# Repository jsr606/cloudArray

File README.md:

# cloud array
github repository for the tech side of the permanent installation "cloud array".

this installation lives permanently at [søndervangskolen](https://soendervangskolen.aarhus.dk/) in viby, århus, denmark. you can see the installation from the inside as well as the outside 24 hours a day, all year.

for more information visit this website www.jacobremin.com/cloudArray

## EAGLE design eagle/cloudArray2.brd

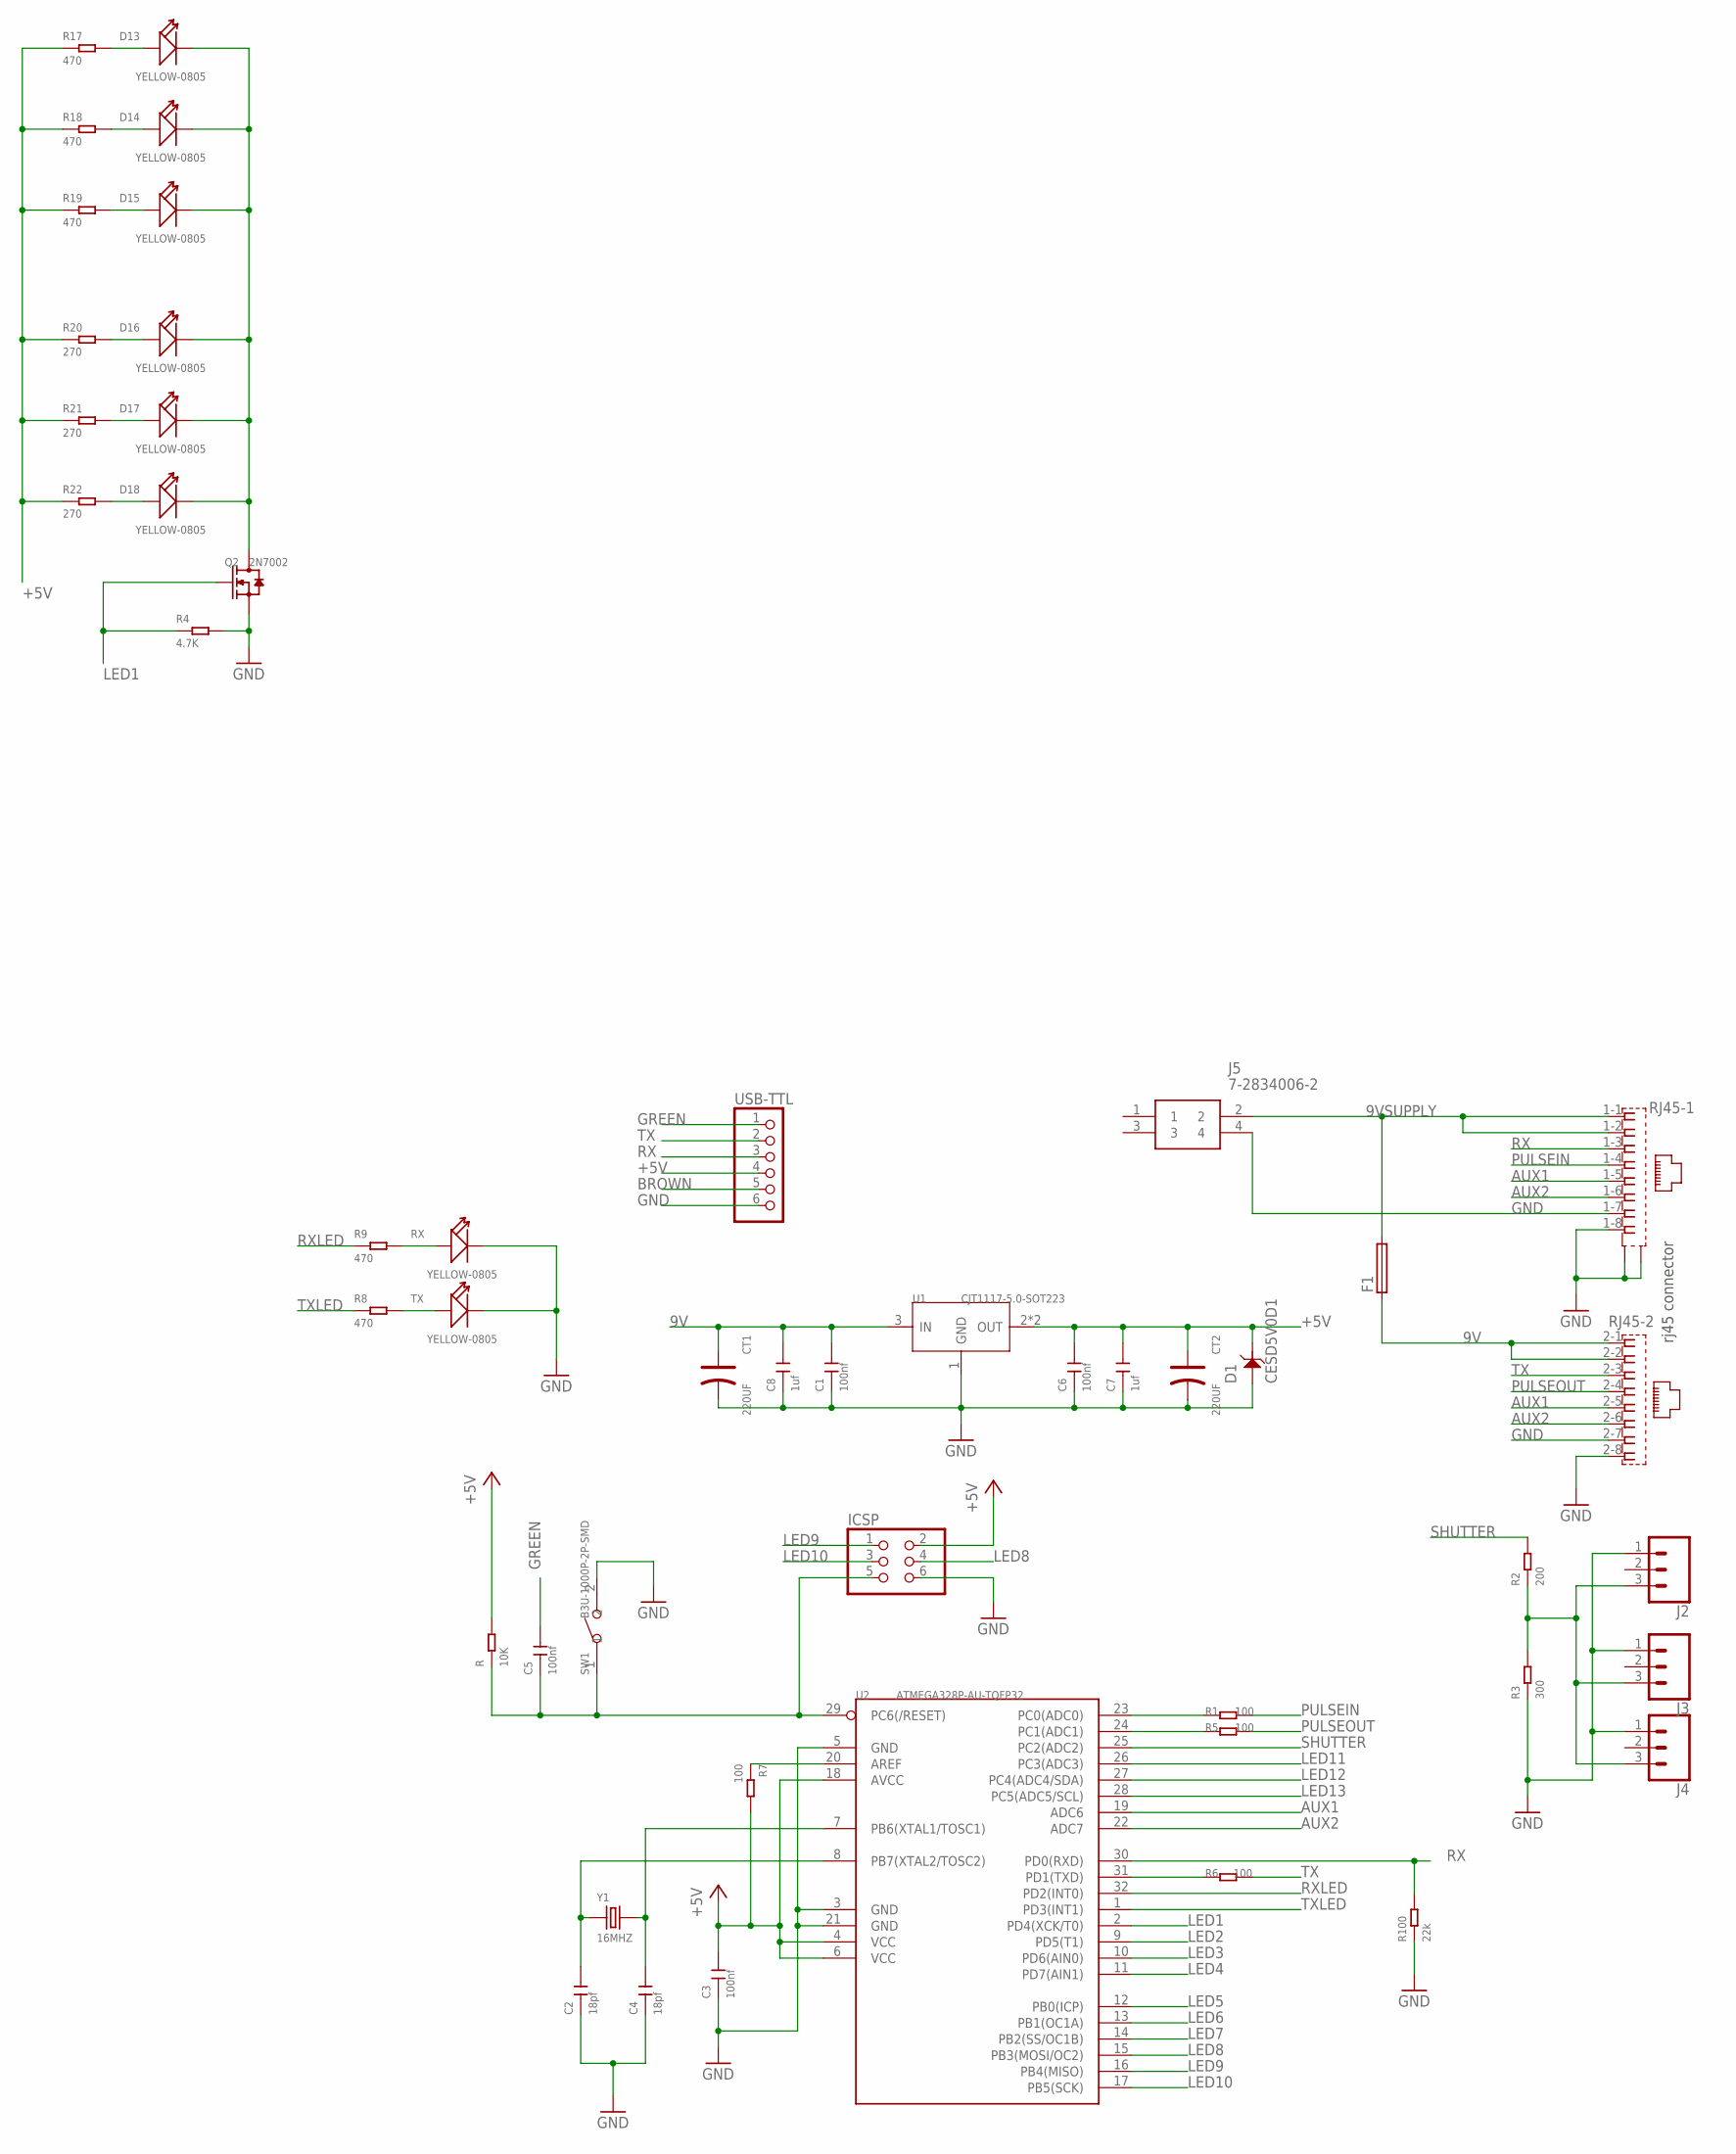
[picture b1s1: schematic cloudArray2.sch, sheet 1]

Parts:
C1, C3, C5, C6: 100nf; C0805
C2, C4: 18pf; C0805
C7, C8: 1uf; C0805
CT1, CT2: 220UF; ELECTRO-SMD-C-6MM
D1: CESD5V0D1; SOD-123
D13, D14, D15, D16, D17, D18: YELLOW-0805; LED-0805
F1: SH22,5A
ICSP: PINHD-2X3; 2X03
J2, J3, J4: 455-1750-1-ND; 1X03
J5: 7-2834006-2; 728340062
Q2: 2N7002; SOT-23
R: 10K; R0805
R1, R5, R6, R7: 100; R0805
R2: 200; R0805
R3: 300; R0805
R4: 4.7K; R0805
R8, R9, R17, R18, R19: 470; R0805
R20, R21, R22: 270; R0805
R100: 22k; R0805
RJ45: 557570-1
RX: YELLOW-0805; LED-0805
SW1: B3U-1000P-2P-SMD; SW2-2.6-3.0X2.5X1.2+0.4MM
TX: YELLOW-0805; LED-0805
U1: CJT1117-5.0-SOT223; SOT-223
U2: ATMEGA328P-AU-TQFP32; TQFP32-0.8-7X7MM
USB-TTL: PINHD-1X6; 1X06
Y1: 16MHZ; X2-SMD-5.0X3.2X1.3MM

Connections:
9V: C1.2, C8.2, CT1.+, F1.1, RJ45.2-1 (1), RJ45.2-2 (2), U1.3 (IN)
9VSUPPLY: F1.2, J5.2, RJ45.1-1 (1), RJ45.1-2 (2)
+5V: C3.2, C6.2, C7.2, CT2.+, D1.- (2), ICSP.2, R.2, R7.2, R17.1, R18.1, R19.1, R20.1, R21.1, R22.1, U1.2 (OUT), U1.TER (OUT), U2.4 (VCC), U2.6 (VCC), U2.18 (AVCC), USB-TTL.4; also elsewhere on the board
A0: R1.2, U2.23 (PC0(ADC0))
A1: R5.2, U2.24 (PC1(ADC1))
AREF: R7.1, U2.20 (AREF)
AUX1: RJ45.1-5 (5), RJ45.2-5 (5), U2.19 (ADC6)
AUX2: RJ45.1-6 (6), RJ45.2-6 (6), U2.22 (ADC7)
BROWN: USB-TTL.5
GND: C1.1, C2.1, C3.1, C4.1, C6.1, C7.1, C8.1, CT1.-, CT2.-, D1.+ (1), ICSP.6, J2.1, J3.1, J4.1, J5.4, Q2.2 (S), R3.1, R4.2, R100.1, RJ45.1-7 (7), RJ45.1-8 (8), RJ45.2-7 (7), RJ45.2-8 (8), RJ45.G1 (S2), RJ45.G3 (S1), RX.-, SW1.2, TX.-, U1.1 (GND), U2.3 (GND), U2.5 (GND), U2.21 (GND), USB-TTL.6; also elsewhere on the board
GREEN: C5.2, USB-TTL.1
LED1: Q2.1 (G), R4.1, U2.2 (PD4(XCK/T0))
LED2: U2.9 (PD5(T1)); also elsewhere on the board
LED3: U2.10 (PD6(AIN0)); also elsewhere on the board
LED4: U2.11 (PD7(AIN1)); also elsewhere on the board
LED5: U2.12 (PB0(ICP)); also elsewhere on the board
LED6: U2.13 (PB1(OC1A)); also elsewhere on the board
LED7: U2.14 (PB2(SS/OC1B)); also elsewhere on the board
LED8: ICSP.4, U2.15 (PB3(MOSI/OC2)); also elsewhere on the board
LED9: ICSP.1, U2.16 (PB4(MISO)); also elsewhere on the board
LED10: ICSP.3, U2.17 (PB5(SCK)); also elsewhere on the board
LED11: U2.26 (PC3(ADC3)); also elsewhere on the board
LED12: U2.27 (PC4(ADC4/SDA)); also elsewhere on the board
LED13: U2.28 (PC5(ADC5/SCL)); also elsewhere on the board
unnamed: D13.-, D14.-, D15.-, D16.-, D17.-, D18.-, Q2.3 (D)
unnamed: C2.2, U2.8 (PB7(XTAL2/TOSC2)), Y1.1
unnamed: C4.2, U2.7 (PB6(XTAL1/TOSC1)), Y1.2
unnamed: R6.2, U2.31 (PD1(TXD))
unnamed: R8.2, TX.+
unnamed: J2.3, J3.3, J4.3, R2.1, R3.2
unnamed: R9.2, RX.+
unnamed: D13.+, R17.2
unnamed: D14.+, R18.2
unnamed: D15.+, R19.2
unnamed: D16.+, R20.2
unnamed: D17.+, R21.2
unnamed: D18.+, R22.2
PULSEIN: R1.1, RJ45.1-4 (4)
PULSEOUT: R5.1, RJ45.2-4 (4)
RESET: C5.1, ICSP.5, R.1, SW1.1, U2.29 (PC6(/RESET))
RX: R100.2, RJ45.1-3 (3), U2.30 (PD0(RXD)), USB-TTL.3
RXLED: R9.1, U2.32 (PD2(INT0))
SHUTTER: R2.2, U2.25 (PC2(ADC2))
TX: R6.1, RJ45.2-3 (3), USB-TTL.2
TXLED: R8.1, U2.1 (PD3(INT1))

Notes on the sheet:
rj45 connector

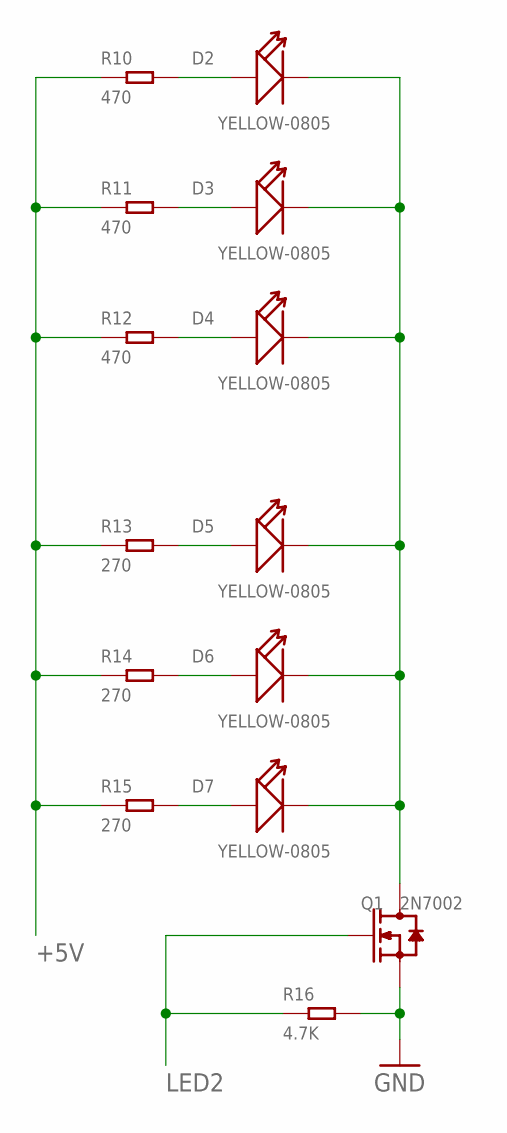
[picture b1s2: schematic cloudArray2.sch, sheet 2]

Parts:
D2, D3, D4, D5, D6, D7: YELLOW-0805; LED-0805
Q1: 2N7002; SOT-23
R10, R11, R12: 470; R0805
R13, R14, R15: 270; R0805
R16: 4.7K; R0805

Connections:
+5V: R10.1, R11.1, R12.1, R13.1, R14.1, R15.1; also elsewhere on the board
GND: Q1.2 (S), R16.2; also elsewhere on the board
LED2: Q1.1 (G), R16.1; also elsewhere on the board
unnamed: D2.+, R10.2
unnamed: D3.+, R11.2
unnamed: D4.+, R12.2
unnamed: D5.+, R13.2
unnamed: D6.+, R14.2
unnamed: D7.+, R15.2
unnamed: D2.-, D3.-, D4.-, D5.-, D6.-, D7.-, Q1.3 (D)

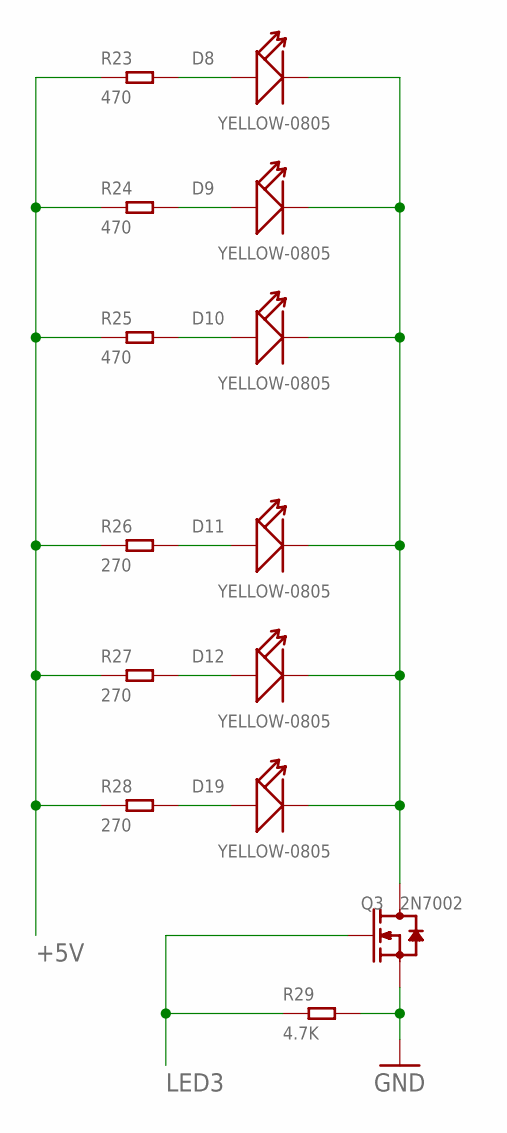
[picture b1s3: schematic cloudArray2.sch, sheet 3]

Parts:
D8, D9, D10, D11, D12, D19: YELLOW-0805; LED-0805
Q3: 2N7002; SOT-23
R23, R24, R25: 470; R0805
R26, R27, R28: 270; R0805
R29: 4.7K; R0805

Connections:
+5V: R23.1, R24.1, R25.1, R26.1, R27.1, R28.1; also elsewhere on the board
GND: Q3.2 (S), R29.2; also elsewhere on the board
LED3: Q3.1 (G), R29.1; also elsewhere on the board
unnamed: D8.+, R23.2
unnamed: D9.+, R24.2
unnamed: D10.+, R25.2
unnamed: D11.+, R26.2
unnamed: D12.+, R27.2
unnamed: D19.+, R28.2
unnamed: D8.-, D9.-, D10.-, D11.-, D12.-, D19.-, Q3.3 (D)

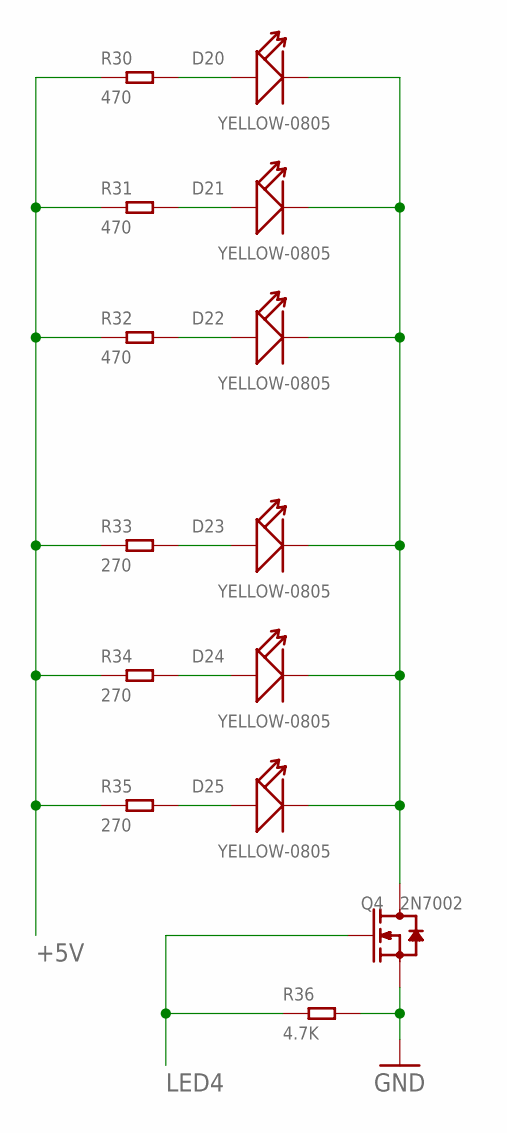
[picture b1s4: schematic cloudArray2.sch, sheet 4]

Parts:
D20, D21, D22, D23, D24, D25: YELLOW-0805; LED-0805
Q4: 2N7002; SOT-23
R30, R31, R32: 470; R0805
R33, R34, R35: 270; R0805
R36: 4.7K; R0805

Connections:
+5V: R30.1, R31.1, R32.1, R33.1, R34.1, R35.1; also elsewhere on the board
GND: Q4.2 (S), R36.2; also elsewhere on the board
LED4: Q4.1 (G), R36.1; also elsewhere on the board
unnamed: D20.+, R30.2
unnamed: D21.+, R31.2
unnamed: D22.+, R32.2
unnamed: D23.+, R33.2
unnamed: D24.+, R34.2
unnamed: D25.+, R35.2
unnamed: D20.-, D21.-, D22.-, D23.-, D24.-, D25.-, Q4.3 (D)

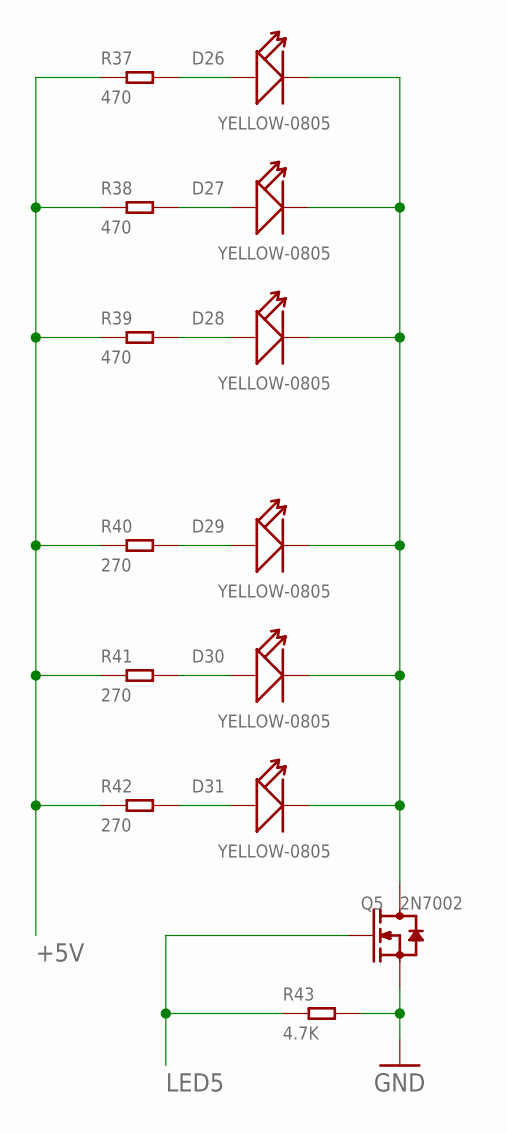
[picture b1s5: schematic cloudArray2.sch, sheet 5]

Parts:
D26, D27, D28, D29, D30, D31: YELLOW-0805; LED-0805
Q5: 2N7002; SOT-23
R37, R38, R39: 470; R0805
R40, R41, R42: 270; R0805
R43: 4.7K; R0805

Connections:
+5V: R37.1, R38.1, R39.1, R40.1, R41.1, R42.1; also elsewhere on the board
GND: Q5.2 (S), R43.2; also elsewhere on the board
LED5: Q5.1 (G), R43.1; also elsewhere on the board
unnamed: D26.+, R37.2
unnamed: D27.+, R38.2
unnamed: D28.+, R39.2
unnamed: D29.+, R40.2
unnamed: D30.+, R41.2
unnamed: D31.+, R42.2
unnamed: D26.-, D27.-, D28.-, D29.-, D30.-, D31.-, Q5.3 (D)

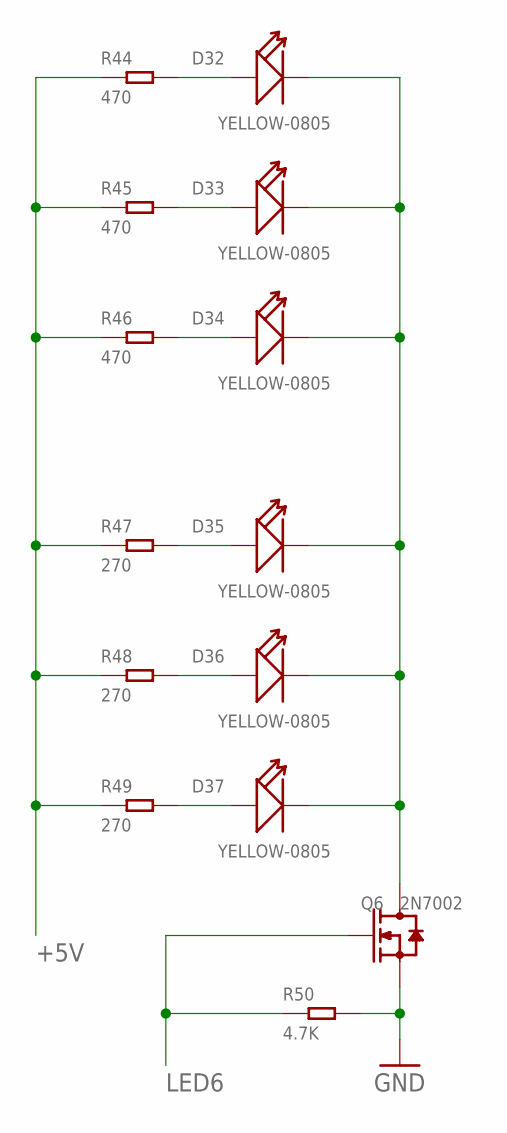
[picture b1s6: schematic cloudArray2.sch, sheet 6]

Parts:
D32, D33, D34, D35, D36, D37: YELLOW-0805; LED-0805
Q6: 2N7002; SOT-23
R44, R45, R46: 470; R0805
R47, R48, R49: 270; R0805
R50: 4.7K; R0805

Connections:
+5V: R44.1, R45.1, R46.1, R47.1, R48.1, R49.1; also elsewhere on the board
GND: Q6.2 (S), R50.2; also elsewhere on the board
LED6: Q6.1 (G), R50.1; also elsewhere on the board
unnamed: D32.+, R44.2
unnamed: D33.+, R45.2
unnamed: D34.+, R46.2
unnamed: D35.+, R47.2
unnamed: D36.+, R48.2
unnamed: D37.+, R49.2
unnamed: D32.-, D33.-, D34.-, D35.-, D36.-, D37.-, Q6.3 (D)

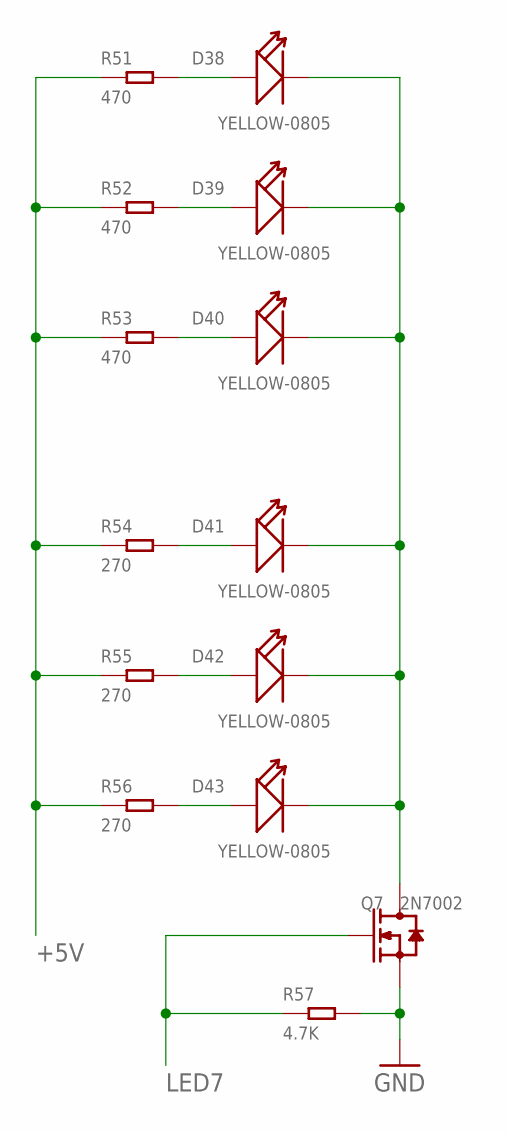
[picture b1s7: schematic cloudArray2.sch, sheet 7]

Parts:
D38, D39, D40, D41, D42, D43: YELLOW-0805; LED-0805
Q7: 2N7002; SOT-23
R51, R52, R53: 470; R0805
R54, R55, R56: 270; R0805
R57: 4.7K; R0805

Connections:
+5V: R51.1, R52.1, R53.1, R54.1, R55.1, R56.1; also elsewhere on the board
GND: Q7.2 (S), R57.2; also elsewhere on the board
LED7: Q7.1 (G), R57.1; also elsewhere on the board
unnamed: D38.+, R51.2
unnamed: D39.+, R52.2
unnamed: D40.+, R53.2
unnamed: D41.+, R54.2
unnamed: D42.+, R55.2
unnamed: D43.+, R56.2
unnamed: D38.-, D39.-, D40.-, D41.-, D42.-, D43.-, Q7.3 (D)

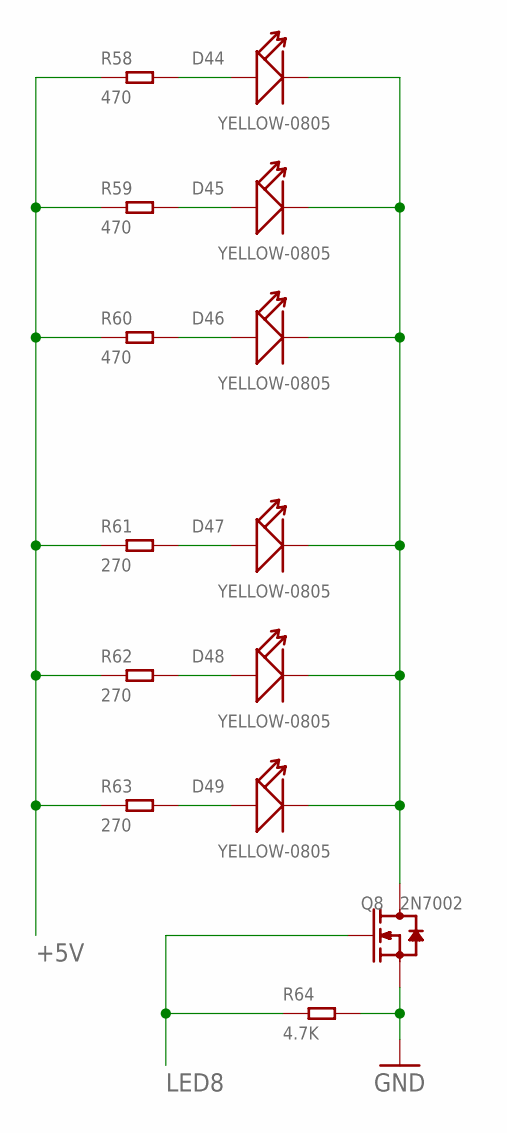
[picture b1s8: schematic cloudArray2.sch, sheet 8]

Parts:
D44, D45, D46, D47, D48, D49: YELLOW-0805; LED-0805
Q8: 2N7002; SOT-23
R58, R59, R60: 470; R0805
R61, R62, R63: 270; R0805
R64: 4.7K; R0805

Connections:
+5V: R58.1, R59.1, R60.1, R61.1, R62.1, R63.1; also elsewhere on the board
GND: Q8.2 (S), R64.2; also elsewhere on the board
LED8: Q8.1 (G), R64.1; also elsewhere on the board
unnamed: D44.+, R58.2
unnamed: D45.+, R59.2
unnamed: D46.+, R60.2
unnamed: D47.+, R61.2
unnamed: D48.+, R62.2
unnamed: D49.+, R63.2
unnamed: D44.-, D45.-, D46.-, D47.-, D48.-, D49.-, Q8.3 (D)

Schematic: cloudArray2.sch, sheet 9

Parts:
D50, D51, D52, D53, D54, D55: YELLOW-0805; LED-0805
Q9: 2N7002; SOT-23
R65, R66, R67: 470; R0805
R68, R69, R70: 270; R0805
R71: 4.7K; R0805

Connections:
+5V: R65.1, R66.1, R67.1, R68.1, R69.1, R70.1; also elsewhere on the board
GND: Q9.2 (S), R71.2; also elsewhere on the board
LED9: Q9.1 (G), R71.1; also elsewhere on the board
unnamed: D50.+, R65.2
unnamed: D51.+, R66.2
unnamed: D52.+, R67.2
unnamed: D53.+, R68.2
unnamed: D54.+, R69.2
unnamed: D55.+, R70.2
unnamed: D50.-, D51.-, D52.-, D53.-, D54.-, D55.-, Q9.3 (D)

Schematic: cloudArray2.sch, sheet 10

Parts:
D56, D57, D58, D59, D60, D61: YELLOW-0805; LED-0805
Q10: 2N7002; SOT-23
R72, R73, R74: 470; R0805
R75, R76, R77: 270; R0805
R78: 4.7K; R0805

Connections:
+5V: R72.1, R73.1, R74.1, R75.1, R76.1, R77.1; also elsewhere on the board
GND: Q10.2 (S), R78.2; also elsewhere on the board
LED10: Q10.1 (G), R78.1; also elsewhere on the board
unnamed: D56.+, R72.2
unnamed: D57.+, R73.2
unnamed: D58.+, R74.2
unnamed: D59.+, R75.2
unnamed: D60.+, R76.2
unnamed: D61.+, R77.2
unnamed: D56.-, D57.-, D58.-, D59.-, D60.-, D61.-, Q10.3 (D)

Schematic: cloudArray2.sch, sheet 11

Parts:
D62, D63, D64, D65, D66, D67: YELLOW-0805; LED-0805
Q11: 2N7002; SOT-23
R79, R80, R81: 470; R0805
R82, R83, R84: 270; R0805
R85: 4.7K; R0805

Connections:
+5V: R79.1, R80.1, R81.1, R82.1, R83.1, R84.1; also elsewhere on the board
GND: Q11.2 (S), R85.2; also elsewhere on the board
LED11: Q11.1 (G), R85.1; also elsewhere on the board
unnamed: D62.+, R79.2
unnamed: D63.+, R80.2
unnamed: D64.+, R81.2
unnamed: D65.+, R82.2
unnamed: D66.+, R83.2
unnamed: D67.+, R84.2
unnamed: D62.-, D63.-, D64.-, D65.-, D66.-, D67.-, Q11.3 (D)

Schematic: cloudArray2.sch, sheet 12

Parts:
D68, D69, D70, D71, D72, D73: YELLOW-0805; LED-0805
Q12: 2N7002; SOT-23
R86, R87, R88: 470; R0805
R89, R90, R91: 270; R0805
R92: 4.7K; R0805

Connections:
+5V: R86.1, R87.1, R88.1, R89.1, R90.1, R91.1; also elsewhere on the board
GND: Q12.2 (S), R92.2; also elsewhere on the board
LED12: Q12.1 (G), R92.1; also elsewhere on the board
unnamed: D68.+, R86.2
unnamed: D69.+, R87.2
unnamed: D70.+, R88.2
unnamed: D71.+, R89.2
unnamed: D72.+, R90.2
unnamed: D73.+, R91.2
unnamed: D68.-, D69.-, D70.-, D71.-, D72.-, D73.-, Q12.3 (D)

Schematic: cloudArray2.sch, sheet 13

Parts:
D74, D75, D76, D77, D78, D79: YELLOW-0805; LED-0805
Q13: 2N7002; SOT-23
R93, R94, R95: 470; R0805
R96, R97, R98: 270; R0805
R99: 4.7K; R0805

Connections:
+5V: R93.1, R94.1, R95.1, R96.1, R97.1, R98.1; also elsewhere on the board
GND: Q13.2 (S), R99.2; also elsewhere on the board
LED13: Q13.1 (G), R99.1; also elsewhere on the board
unnamed: D74.+, R93.2
unnamed: D75.+, R94.2
unnamed: D76.+, R95.2
unnamed: D77.+, R96.2
unnamed: D78.+, R97.2
unnamed: D79.+, R98.2
unnamed: D74.-, D75.-, D76.-, D77.-, D78.-, D79.-, Q13.3 (D)

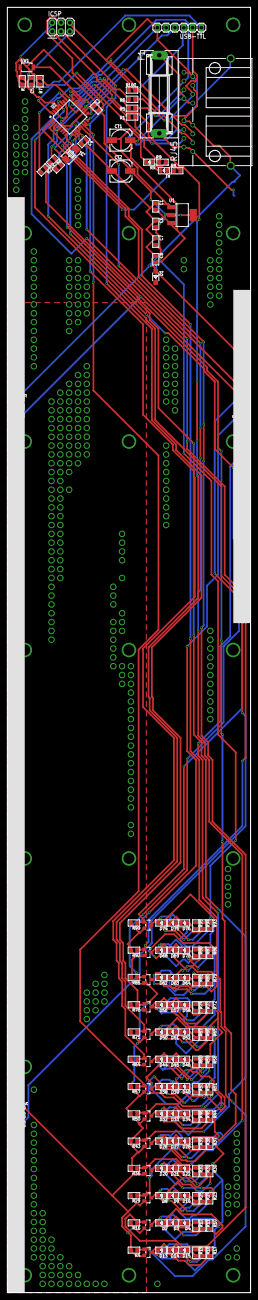
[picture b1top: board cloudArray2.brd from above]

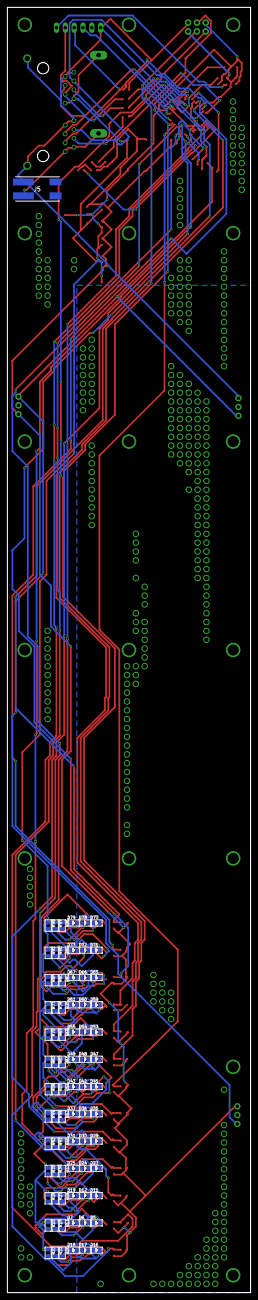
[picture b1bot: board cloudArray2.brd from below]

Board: 2 copper layers, 70.0 x 370.0 mm, 217 parts (79 on the bottom side), 128 nets.

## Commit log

2020-02-06 double spaces
2020-02-06 eagle files are too messy
2020-02-11 final arduino, added pics, readme updated
2020-02-16 documentation
2020-02-16 more documentation

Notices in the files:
parts and their libraries:
SparkFun-Connectors: Licensing: Creative Commons ShareAlike 4.0 International - https://creativecommons.org/licenses/by-sa/4.0
